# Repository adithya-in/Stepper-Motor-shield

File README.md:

# Stepper Motor Shield — PID Position Control + S-Curve

PIC32MK0512MCJ064 firmware driving a NEMA17 stepper via TB6600 driver with AS5047U
magnetic encoder feedback. Controlled over USB serial (115200 baud) or web dashboard.

**Achieved accuracy: ±1–3 encoder counts = 0.022°–0.066°** (limited by encoder noise floor).

**Clock speed note:** All testing done at **48 MHz** SYSCLK (SPLL from 8 MHz FRC). Target production clock is **10 MHz** (external crystal or lower PLL) — testing pending.

## Project Status

| Area | Status |
|------|--------|
| **Firmware** | **Complete** — v6.2.0 tested and verified at 48 MHz (SPLL, 115200 baud, auto-tune capped) |
| **Hardware testing** | **Complete** — NEMA17 + TB6600 characterized at 24V and 31V (see test data below) |
| **Schematic** | **Complete** — KiCad schematic for PIC32MK + TMC2660 + AS5047D + CAN + USB-C (`hardware/Motorshield v6.kicad_sch`) |
| **PCB layout** | **In progress** — routing and layout yet to be finished |
| **10 MHz migration** | **Pending** — clock-dependent formulas need recalculation and retesting |

## Quick Start

```bash
# Flash firmware (via MDB)
rm -rf ~/.mplabcomm
/Applications/microchip/mplabx/v6.30/mplab_platform/bin/mdb.sh flash.mdb

# Connect serial
screen /dev/cu.usbmodemBUR2143200772 115200

# Start dashboard
cd dashboard && npm install && node server.js
# → http://localhost:3000
```

**Power cycle the PKoB4** (unplug/replug USB) after flashing — VCOM gets stuck otherwise.

## Serial Commands

All commands support both **legacy** and **Phase 1** formats. Legacy commands are preserved
so the dashboard and existing scripts continue working.

### Legacy Commands

| Command | Action | Range |
|---------|--------|-------|
| **Position Control** | | |
| `T=<pos>` | Move to absolute position (encoder counts, negative OK) | ±2M |
| `STOP` | Emergency stop — hold position, reset integrator | — |
| `HOME` | Set current position = 0 AND target = 0 | — |
| `ZERO` | Set current position = 0 (leave target unchanged) | — |
| `CLEAR` | Clear fault, re-init motor driver | — |
| **Open-Loop Motor Test** | | |
| `ON` | Enable motor + start spinning at last speed (default 100) | — |
| `OFF` | Disable motor, exit open-loop mode | — |
| `CW` | Set direction clockwise | — |
| `CCW` | Set direction counter-clockwise | — |
| `SPEED=<n>` | Set step rate for open-loop mode | 10–100000 |
| **Motion Profile** | | |
| `MAXV=<n>` | Max velocity | ≥1 steps/s |
| `ACCEL=<n>` | Max acceleration | ≥100 steps/s² |
| `JERK=<n>` | Max jerk (S-curve smoothness) | ≥1000 steps/s³ |
| `PROFILE=S` | S-curve — jerk-limited smooth transitions | — |
| `PROFILE=T` | Trapezoidal — instant acceleration changes | — |
| **PID Tuning** | | |
| `KP=<n>` | Proportional gain | 0–99999 |
| `KI=<n>` | Integral gain | 0–99999 |
| `KD=<n>` | Derivative gain | 0–99999 |
| `TOL=<n>` | At-target tolerance | 0–1000 counts |
| `FT=<n>` | Fault threshold (checked only at rest) | 1–100000 counts |
| **Diagnostics** | | |
| `GET` | One-shot config dump | — |
| **Multi-Point Queue** | | |
| `Q=<pos>,<pos>,...` | Load queue (2–32 points) and start sequential execution | — |
| `DWELL=<ms>` | Set inter-point dwell delay (0–30000 ms) | — |
| `QSTOP` | Abort queue mid-execution | — |

### Phase 1 Commands (Colon-Separated)

| Command | Action | Example |
|---------|--------|---------|
| **Move** | | |
| `m:<speed>:<pos>` | Move to position at given speed (sets MAXV temporarily) | `m:20000:80000` |
| **Enable** | | |
| `en:1` | Enable closed-loop servo (hold current position) | `en:1` |
| `en:0` | Disable motor (release) | `en:0` |
| **Zero** | | |
| `z` | Set current encoder position as zero | `z` |
| **Coil Current (stored)** | | |
| `i:<mA>` | Set coil current limit (stored value, 100–5000 mA) | `i:800` |
| **Microstep (stored)** | | |
| `us:<n>` | Set microstep setting (1/2/4/8/16/32) | `us:16` |
| **PID Gains** | | |
| `pid:<kp>:<ki>:<kd>` | Set proportional, integral, derivative gains | `pid:50:5:10` |
| **Telemetry** | | |
| `tlm:1:<ms>` | Enable status stream at N ms period | `tlm:1:50` |
| `tlm:0` | Disable status stream | `tlm:0` |
| **Multi-Point Queue** | | |
| `q:<pos1>:<pos2>:...` | Load queue (2–32 points) and start sequential execution | `q:10000:20000:30000` |
| `dwell:<ms>` | Set inter-point dwell delay | `dwell:1000` |
| `qstop` | Abort queue mid-execution | `qstop` |
| **Status Query** | | |
| `st?` | One-shot status: position, velocity, error, flags | `st?` |

### Response Format

All commands acknowledge:
```
OK <command>=<value>\r\n
```
or
```
ERR UNKNOWN\r\n
```

### Automatic Status Stream (10 Hz default)

```
P:<position>,E:<error>,V:<velocity>,T:<target>,F:<fault>,M:<moving>,A:<at_target>,Q:<qidx>,QL:<qlen>\r\n
```

Set period with `tlm:1:<ms>` (10–10000 ms), disable with `tlm:0`.

### st? Response (one-shot)

```
p:<position>,v:<velocity>,e:<error>,f:<flags>\r\n
```

Flags bitmask:
- bit 0: fault
- bit 1: moving
- bit 2: at_target
- bit 3: open_loop

### GET Response

```
T=<target>,P=<position>,E=<error>,V=<velocity>,KP=<kp>,KI=<ki>,KD=<kd>,MAXV=<maxv>,ACCEL=<accel>,JERK=<jerk>,TOL=<tol>,FT=<ft>,PROFILE=<S|T>,I=<mA>,US=<microstep>,QLEN=<n>,QIDX=<n>,DWELL=<ms>\r\n
```

## Usage Examples

### Basic Move

```
> en:1           Enable servo (holds current position)
OK en:1
> m:20000:50000  Move to position 50000 at 20000 steps/s
OK m:20000:50000
> st?            Check status
p:50000,v:0,e:0,f:4
```

### Snappy Move (profile feed-forward)

The motor runs at full commanded speed until the stopping distance
(`v² / (2·accel_limit)`) from target, then decelerates hard. The PID
acts as a trim, active only near the target.

```
> PROFILE=T      Trapezoidal profile (instant accel changes)
> ACCEL=500000   Fastest ramp
> MAXV=50000     Top speed
OK PROFILE=T
OK ACCEL=500000
OK MAXV=50000
> m:50000:100000 Move at 50000 steps/s — reaches full speed in ~100ms
OK m:50000:100000
```

### PID Tuning

```
> pid:30:2:5     Set Kp=30, Ki=2, Kd=5
OK pid:30:2:5
> GET            Verify all params
T=10000,P=10000,E=0,V=0,KP=30,KI=2,KD=5,...
```

### Auto-Tune

Relay-based Ziegler-Nichols PID tuning. The motor oscillates around a target, measures ultimate gain (Ku) and period (Tu), then applies:

```
Kp = 0.6 × Ku × 100    (capped at 10000)
Ki = 1.2 × Ku / Tu      (capped at 1000)
Kd = 0.075 × Ku × Tu    (capped at 10000)
```

Send `TUNE` to start. The motor will:
1. Move to current position + 3000 counts
2. Begin relay oscillation (±3000 steps/s relay velocity)
3. After 4+ full cycles, compute PID gains
4. Report: `OK TUNE:Kp=...,Ki=...,Kd=...,amp=...,Tu=...`
5. Return to original target

Caps on auto-tune output prevent excessive gains that cause oscillation — particularly Kd, which can destabilize the motor at high values.

### Telemetry Stream

```
> tlm:1:200      Stream every 200ms
OK tlm:1:200
P:5000,E:-2,V:150,T:5000,F:0,M:0,A:1
P:5000,E:-1,V:0,T:5000,F:0,M:0,A:1
...
> tlm:0          Stop streaming
OK tlm:0
```

### Multi-Point Queue

```
> DWELL=2000     Set 2 second pause between points
OK DWELL=2000
> Q=10000,30000,50000,20000  Load 4-waypoint queue
OK Q=4 points
> ...automatically moves: 10000 → 30000 → 50000 → 20000...
                Each arrival: 2s dwell → next move
> QSTOP          Abort mid-sequence
OK QSTOP
```

Queue is automatically aborted on any manual move (`T=`, `m:`), `STOP`, `OFF`, or `en:0`.

## Accuracy

The system achieves **±1–3 encoder counts** following error at rest.

| Domain | Value |
|--------|-------|
| 1 encoder count | 360° / 16384 = **0.022°** |
| Typical error | 1–3 counts = **0.022°–0.066°** |
| AS5047U non-linearity | ±0.05° = ~±2 counts |
| With 10mm leadscrew | 1 count ≈ **0.6 µm** |

The error is at the encoder's own noise floor. No further improvement possible
without a higher-resolution encoder.

## Non-Volatile Config

All tuning parameters (Kp, Ki, Kd, max_vel, accel_limit, jerk_limit, tolerance,
fault_thr, profile, coil_current, microstep) are automatically saved to the last
flash page when changed. Persist across power cycles.

- **Flash address**: last page of 512KB (0x1D07F000)
- **Save strategy**: 100ms debounce after last parameter change
- **Integrity**: magic word (0xBEADC0DE) + XOR checksum validated on load
- **Defaults**: used if flash is blank or corrupted

## Motion Profiles

### S-Curve (`PROFILE=S`)
Jerk-limited acceleration:

```
acceleration:  ──/‾‾‾‾‾‾\──  (ramps up/down at JERK rate)
velocity:      ──/‾‾‾‾‾‾\──  (rounded S-shaped transitions)
```

- Jerk limits how fast acceleration changes
- Lower JERK = smoother but slower moves
- Three phases: smooth accel → coast → smooth decel

### Trapezoidal (`PROFILE=T`)
Instant acceleration changes:

```
acceleration:  ──╯‾‾‾‾‾‾╰──  (square wave)
velocity:      ──/‾‾‾‾‾‾\──  (sharp V-shaped ramps)
```

- ACCEL limits the slope of velocity ramps
- Reaches target speed faster than S-curve at same ACCEL
- Higher mechanical stress at transitions

### Profile Feed-Forward (v5.1.2+)

The velocity target is computed from a motion profile, not from PID error.
The motor maintains full commanded speed until the stopping distance from target,
then decelerates at the ACCEL rate. PID adds only a small trim for fine positioning.

```
raw_vel = profile_velocity(error) + pid_trim
profile_vel = max_vel (if far) or linear decel ramp (near target)
pid_trim    = (Kp·error + Ki·integral + Kd·derivative) / 100
```

Anti-windup: integral resets during moves, only active near target.
Auto-tune output capped at Kp≤10000, Ki≤1000, Kd≤10000 to prevent excessive gains.

## Wiring

See [PINOUT.md](docs/PINOUT.md) for complete pin mapping.

### TB6600 Common-Anode Summary

| TB6600 | PIC32MK | Note |
|--------|---------|------|
| PUL+ | RPB15 (OC1 PWM) | Step pulses, 50% duty |
| DIR+ | RPB14 (GPIO) | LOW=CW, HIGH=CCW |
| ENA+ | RPB13 (GPIO) | **LOW=enable**, HIGH=disable |
| PUL-/DIR-/ENA- | GND | All three tied together |

### TB6600 DIP Switches
- S1/S2/S3: per motor current rating
- S4/S5/S6: S4 ON, S5 ON, S6 ON = 1/32 microstep (6400 steps/rev)

## Dashboard

Web-based UI on port 3000:

```
dashboard/
├── server.js          # Express + WebSocket + serial bridge
├── package.json
└── public/
    ├── index.html     # UI layout
    ├── app.js         # Client logic
    └── styles.css     # Dark theme
```

### Features
- Position display: target / actual with bar indicator
- Status: error, velocity, fault, moving, at-target
- Motor Test card: ON/OFF, CW/CCW, speed slider (up to 50000 steps/s)
- PID sliders: Kp (0–50000), Ki (0–10000), Kd (0–50000)
- Auto-tune button: relay-based Ziegler-Nichols tuning, results shown with slider label sync
- TLM toggle: enable/disable telemetry stream
- Motion Profile: S-curve / Trapezoidal toggle
- ACCEL and JERK number inputs with Set buttons
- MAXV, Tolerance, Fault Threshold inputs
- GET response parsing: position, error, velocity, TOL, FT fields

### Architecture

```
Firmware (PIC32MK) ←→ Serial (115200) ←→ server.js ←→ WebSocket ←→ browser
```

## Firmware Architecture

**Clock:** Currently runs at **48 MHz** (SPLL from 8 MHz FRC). Target for production: **10 MHz** — all clock-dependent formulas (core timer, UART baud, step pulse generation, auto-tune timing) will need recalculation. Testing at 10 MHz is pending.

| Component | Peripheral | Rate | Purpose |
|-----------|-----------|------|---------|
| Position loop | Timer3 ISR | 1 kHz | Profile → PID trim → smoother → velocity |
| Step generation | OC1 + Timer2 PWM | Variable | Hardware step pulses, 50% duty |
| Encoder | QEI1 | Continuous | AS5047U ABI, 16384 counts/rev |
| UART | UART1 | 115200 baud | Command + telemetry |
| NVM flash | Self-write | On change | Config storage (last flash page) |
| Status stream | Main loop | Configurable | P:E:V:T:F:M:A:Q:QL telemetry |

### Algorithm

```
error = target_pos - encoder_read()

// Profile feed-forward velocity
stop_dist = max_vel² / (2 × accel_limit)     // stopping distance
if abs(error) > stop_dist:
    profile_vel = max_vel × sign(error)       // cruise
else:
    profile_vel = max_vel × error / stop_dist // decel ramp

// PID trim
pid_trim = (Kp×error + Ki×integral + Kd×derivative) / 100

// Combined, fed into accel/jerk smoother
raw_vel = profile_vel + pid_trim

// Accel/jerk smoother → sm_vel → motor steps
```

### Resolution

| Aspect | Value |
|--------|-------|
| Motor steps/rev | 200 (NEMA17, 1.8°/step) |
| Microstep setting | **1/32** (S4 ON, S5 ON, S6 ON) |
| Steps per revolution | **6400** |
| Encoder PPR | 4096 (AS5047U) |
| Encoder counts/rev (4× QEI) | 16384 |
| Position resolution | 360° / 16384 = **0.022°** per count |

## Voltage-Dependent Limits

At **1/32 microstep** (6400 steps/rev). Firmware accepts any positive value; the
practical limit is set by the motor driver and supply voltage. Empirically determined
guidelines (no load, idle condition):

| Supply Voltage | MAXV (steps/s) | MAXV (RPM) | ACCEL (steps/s²) | Notes |
|----------------|----------------|------------|------------------|-------|
| 31V | 280,000 | 2,625 | 2,700,000 | Best reliable: 1725 mm/s, Kp=2121 Ki=46. All tests at 48 MHz — 10 MHz testing pending |
| 24V | 250,000 | 2,344 | 3,200,000 | At ≥2.5A coil current, smooth with heating. All tests at 48 MHz — 10 MHz testing pending |
| 12V | 50,000 | 469 | 5,000,000 | Reduced max velocity. All tests at 48 MHz — 10 MHz testing pending |

**31V characterization** (from `docs/TESTS.md`):
- MAXV 300k with 3.2M ACCEL reaches 1902 mm/s (Kp 50–1000, Ki=5, Kd=0)
- Kp >~2000 with Ki > 0 causes oscillation at 31V; best results use moderate Kp
- Trade-off: higher MAXV requires lower ACCEL and vice versa
- Kd was 0 in all 31V tests — derivative not needed with proper Kp/Ki balance

**RPM formula:** `RPM = (steps/s × 60) ÷ steps_per_rev` where `steps_per_rev = 6400` at 1/32.

## Releases

| Tag | Date | Description |
|-----|------|-------------|
| **v6.2.0** | 2026-06-20 | **Auto-tune caps restored, 31V test data.** Kp≤10000/Ki≤1000/Kd≤10000 caps restored on auto-tune output (prevents oscillation from excessive gains). 31V characterization: 280k MAXV / 2.7M ACCEL / 1725 mm/s reliable belt speed. |
| **v6.1.0** | 2026-06-17 | **SPLL clock (48 MHz), 115200 baud, no command limits.** FRC→SPLL migration. All clock timing fixed. MAXV/ACCEL/JERK upper limits removed. Dashboard TLM toggle. |
| **v6.0.0** | 2026-06-15 | **Phase 1 complete.** `docs/BUGS_AND_LESSONS.md` — full 24+ bug knowledge base. Dashboard activeElement input protection. |
| **v5.2.0** | 2026-06-12 | Multi-point queue (Q=/q:), DWELL, QSTOP, dashboard queue card |
| **v5.1.4** | 2026-06-12 | Dashboard UI ranges match firmware; ACCEL/JERK number inputs; accuracy ±1–3 counts |
| **v5.1.3** | 2026-06-12 | Snappier defaults: MAXV=5000, ACCEL=50000, JERK=500000; ranges increased 5–10× |
| **v5.1.2** | 2026-06-12 | Profile feed-forward velocity; full speed until stopping distance; PID trim only near target |
| **v5.1.1** | 2026-06-12 | NVM flash config: all settings persist across power cycles |
| **v5.1.0** | 2026-06-12 | Phase 1 commands (colon-separated), Kd, configurable telemetry |
| **v5.0.1** | 2026-06-11 | Trapezoidal profile, dashboard toggle, ACCEL/JERK commands |
| **v5.0.0** | 2026-06-11 | PID + S-curve + open-loop test + 6 bug fixes |
| **v4.0.0** | 2026-06-10 | UART serial fixes |
| **v3.1.0** | 2026-06-09 | Open-loop speed control |
| **v3.0.0** | 2026-06-09 | Closed-loop position control |
| **v2.0.0** | 2026-06-09 | Stepper control + encoder |
| **v1.0.0** | 2026-06-08 | Encoder-only firmware |

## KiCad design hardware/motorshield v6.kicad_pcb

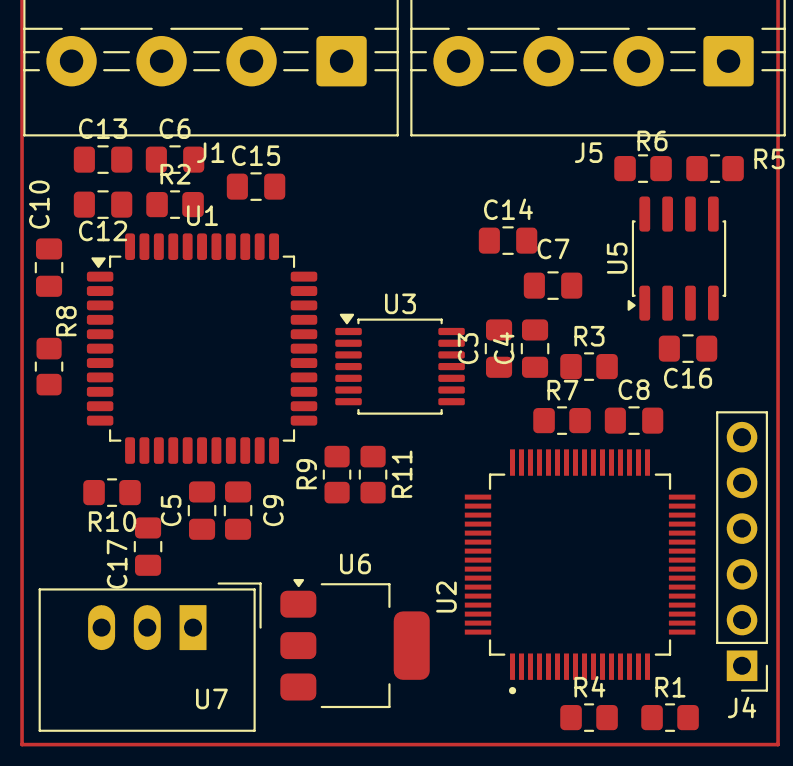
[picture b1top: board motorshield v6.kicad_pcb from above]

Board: 2 copper layers, 34 parts (0 on the bottom side), 42 nets, no tracks yet.

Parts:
C3: 10 µF; C_0805_2012Metric_Pad1.18x1.45mm_HandSolder
C4, C5, C6: 0.1 µF; C_0805_2012Metric_Pad1.18x1.45mm_HandSolder
C7, C8: 21 pF; C_0805_2012Metric_Pad1.18x1.45mm_HandSolder
C9, C12, C13: 1µF; C_0805_2012Metric_Pad1.18x1.45mm_HandSolder
C10: 100nF; C_0805_2012Metric_Pad1.18x1.45mm_HandSolder
C14, C16: 100nF/50V; C_0805_2012Metric_Pad1.18x1.45mm_HandSolder
C15: 220nF; C_0805_2012Metric_Pad1.18x1.45mm_HandSolder
C17: 470nF; C_0805_2012Metric_Pad1.18x1.45mm_HandSolder
J1, J5: Conn_01x04; TerminalBlock_MaiXu_MX126-5.0-04P_1x04_P5.00mm
J4: Conn_01x06; PinHeader_1x06_P2.54mm_Vertical
R1, R4, R7: 1K; R_0805_2012Metric_Pad1.20x1.40mm_HandSolder
R2: 10K; R_0805_2012Metric_Pad1.20x1.40mm_HandSolder
R3: 0 Ω; R_0805_2012Metric_Pad1.20x1.40mm_HandSolder
R5, R6: 120; R_0805_2012Metric_Pad1.20x1.40mm_HandSolder
R8, R11: 0R075; R_0805_2012Metric_Pad1.20x1.40mm_HandSolder
R9, R10: 10R; R_0805_2012Metric_Pad1.20x1.40mm_HandSolder
U1: TMC2660; LQFP-44_10x10mm_P0.8mm
U2: PIC32MK0512MCJ064T-I_PT; PIC32MK0512MCJ064-I_PT
U3: AS5047D; TSSOP-14_4.4x5mm_P0.65mm
U5: MCP2562-E-SN; SOIC-8_3.9x4.9mm_P1.27mm
U6: AMS1117-3.3; SOT-223-3_TabPin2
U7: TSR_1-2450; Converter_DCDC_TRACO_TSR-1_THT

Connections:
+3.3V: C3.1, C4.1, C5.1, C9.1, C16.1, J4.2, R2.2, U1.40 (VCC_IO), U2.10 (VDD), U2.19 (AVDD), U2.26 (VDD), U2.38 (VDD), U2.57 (VDD), U3.12 (VDD3V3), U5.5 (Vio), U6.2 (VO)
+5V: U6.3 (VI), U7.3 (Vout)
+40V: C10.2, C12.1, C13.1, C14.1, C15.1, J5.4, U1.4 (VSA), U1.30 (VSB), U1.36 (VS), U3.11 (VDD), U7.1 (Vin)
/CAN1_RX: U2.36 (AN46/CVD46/RPA14/RA14), U5.4 (RXD)
/CAN1_TX: U2.37 (AN47/CVD47/RPA15/RA15), U5.1 (TXD)
/CANH: J5.2, R6.2
/CANL: J5.1, R5.2
/CSN: U1.18 (~CS), U2.32 (FLT15/RPB4/SCL2/RB4)
/Clock: U2.15 (PGD3/VREF-/OA2IN-/AN2/C2IN1-/RPB0/CTED2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), U3.2 (CLK)
/DIR: U1.41 (DIR), U2.2 (RPB14/PWM1H/RB14)
/ENABLE: U1.19 (~EN), U2.63 (RPB13/PWM2L/CTPLS/RB13)
/Encoder A: U2.4 (AN19/CVD19/RPG6/PWM7L/RG6), U3.7 (A)
/Encoder B: U2.5 (AN18/CVD18/RPG7/PWM7H/RG7), U3.6 (B)
/MCLR: J4.1, R1.2, U2.7 (~MCLR)
/Miso: U2.17 (PGC1/OA1IN+/AN4/C1IN1+/C1IN3-/C2IN3-/RP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), U3.3 (MISO)
/Mosi: U2.16 (PGC3/OA1OUT/VREF+/AN3/C1IN4-/C4IN2-/RPB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), U3.4 (MOSI)
/Motor A+: J1.4, U1.2 (OA1), U1.3 (OA1), U1.7 (OA1), U1.8 (OA1)
/Motor A-: J1.3, U1.5 (OA2), U1.6 (OA2), U1.10 (OA2), U1.11 (OA2)
/Motor B+: J1.2, U1.26 (OB1), U1.27 (OB1), U1.31 (OB1), U1.32 (OB1)
/Motor B-: J1.1, U1.23 (OB2), U1.24 (OB2), U1.28 (OB2), U1.29 (OB2)
/NC: J4.6, U1.1 (n.c.), U1.33 (n.c.), U3.8 (W/PWM), U3.9 (V), U3.10 (U), U3.14 (I/PWM)
/OSCI: C8.1, U2.39 (OSCI/CLKI/AN49/CVD49/RPC12/RC12)
/OSCO: R3.2, U2.40 (OSCO/CLKO/RPC15/RC15)
/SCK: U1.16 (SCK), U2.43 (PGD2/RPB5/SDA1/RB5)
/SDI: U1.15 (SDI), U2.46 (OA5OUT/AN25/CVD25/C5IN4-/RPB7/SCK1/INT0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)
/SDO: U1.14 (SDO), U2.44 (PGC2/RPB6/SCL1/RB6)
/STEP: U1.42 (STEP), U2.3 (RPB15/PWM1L/RB15)
/cs: U2.18 (PGD1/OA1IN-/AN5/CTCMP/C1IN1-/RTCC/RPB3/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), U3.1 (~CS)
GND: C3.2, C4.2, C5.2, C6.2, C7.2, C8.2, C9.2, C10.1, C12.2, C13.2, C14.2, C16.2, C17.1, J4.3, J5.3, R4.1, R7.2, R8.2, R11.2, U1.17 (GND), U1.39 (GND), U1.43 (TST_MODE), U1.44 (GND), U2.9 (VSS), U2.20 (AVSS), U2.25 (VSS), U2.41 (VSS), U2.56 (VSS), U3.5 (TST), U3.13 (GND), U5.2 (VSS), U5.8 (STBY), U6.1 (GND), U7.2 (GND)
unnamed: C7.1, R3.1
unnamed: C6.1, R1.1, R2.1
unnamed: C17.2, U1.13 (5VOUT)
unnamed: R8.1, R10.2, U1.9 (BRA)
unnamed: R9.2, R11.1, U1.25 (BRB)
unnamed: R10.1, U1.12 (SRA)
unnamed: R9.1, U1.22 (SRB)
unnamed: C15.2, U1.35 (VHS)
unnamed: R4.2, U2.1 (TCK/RPA7/PWM4L/RA7), U2.11 (AN10/CVD10/RPA12/FLT13/RA12), U2.12 (AN9/CVD9/RPA11/FLT14/RA11), U2.13 (OA2OUT/AN0/C2IN4-/C4IN3-/RPA0/RA0), U2.14 (OA2IN+/AN1/C2IN1+/RPA1/RA1), U2.31 (TDI/DAC2/AN26/CVD26/RPA8/SDA2/RA8), U2.33 (OA5IN+/AN24/CVD24/C5IN1+/C5IN3-/RPA4/RA4), U2.64 (TDO/PWM4H/RA10)
unnamed: R7.1, U2.21 (OA3OUT/AN6/CVD6/C3IN4-/C4IN1+/C4IN4-/RP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), U2.22 (OA3IN-/AN7/CVD7/C3IN1-/C4IN1-/RPC1/RC1), U2.23 (OA3IN+/AN8/CVD8/C3IN1+/C3IN3-/RPC2/FLT3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), U2.24 (AN11/CVD11/C1IN2-/FLT4/RC11), U2.27 (AN12/CVD12/C2IN2-/C5IN2-/FLT5/RE12), U2.28 (AN13/CVD13/C3IN2-/FLT6/RE13), U2.29 (AN14/CVD14/RPE14/FLT7/RE14), U2.30 (AN15/CVD15/RPE15/FLT8/RE15), U2.34 (AN40/CVD40/RPE0/RE0), U2.35 (AN41/CVD41/RPE1/RE1), U2.42 (RD8), U2.45 (DAC1/AN48/CVD48/RPC10/RC10), U2.47 (SOSCI/RPC13/RC13), U2.50 (TRCLK/RPC6/PWM6H/RC6), U2.51 (TRD0/RPC7/PWM6L/RC7), U2.52 (TRD1/RPC8/PWM5H/RC8), U2.53 (TRD2/RPD5/PWM9H/RD5), U2.54 (TRD3/RPD6/PWM9L/RD6), U2.55 (RPC9/PWM5L/RC9), U2.58 (RPF0/PWM8H/RF0), U2.59 (RPF1/PWM8L/RF1)
unnamed: U2.6 (AN17/CVD17/RPG8/RG8), U2.8 (AN16/CVD16/RPG9/FLT12/RG9)
unnamed: R6.1, U5.7 (CANH)
unnamed: R5.1, U5.6 (CANL)

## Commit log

2026-06-06 Initial commit: AS5047U encoder QEI + UART firmware for PIC32MK MCJ Curiosity Pro
2026-06-06 Add web dashboard, change UART baud to 115200
2026-06-08 Fix UART serial output: PB1DIV clock divider, PPS lock bits, and baud rate
    Bugs fixed (in order of discovery):
    1. CFGCON address was 0xBF80F610 (nonexistent) → changed to 0xBF800000
    - This caused PPS unlock to crash the MCU, no code ever ran
    2. PB1CLK defaults to SYSCLK/2 (4 MHz), not 8 MHz
    - Hardcoded PB_CLOCK=8000000 gave wrong baud (8.5% error at 38400)
    - Changed to PB_CLOCK=4000000 with UART_BAUD=19200 (0.16% error)
2026-06-08 Add CHANGELOG.md for v1.0.0
2026-06-09 v2.0.0: TB6600 stepper control + encoder feedback + full test documentation
    - Add OC1-based step generation (Timer2 PWM, RPB15, 10 kHz)
    - Add direction control (RPB14) and enable (RPB13, LOW=enable)
    - CW 5s → CCW 5s test loop with UART RPM reporting
    - Fix ENA polarity for common-anode wiring (ENA_ON=0)
    - docs/TESTS.md: full journey from Arduino prototyping through PIC32MK
    - docs/PINOUT.md: complete wiring reference with physical pin numbers
2026-06-09 v3.0.0: Closed-loop position control + PI controller + web dashboard
    - Timer3 position control loop at 1 kHz with PI controller
    - OC1/Timer2 variable-rate step generation (10-5000 steps/s)
    - Following error computation with configurable fault threshold
    - Software zero reference (HOME command)
    - Point-to-point moves with configurable position tolerance
    - Coil current limit enforced via MAXV cap
2026-06-09 v3.1.0: Speed control mode — motor spins from browser slider
    - Replace closed-loop position control with open-loop speed control
    - Commands: ON OFF CW CCW SPEED <steps/s>
    - Dashboard: RPM gauge, speed slider (0-10000), direction toggle, start/stop
    - Encoder RPM feedback displayed live in browser
    - Clean build, no errors
2026-06-09 Auto-start motor at 2000 steps/s CW on boot
2026-06-09 Add encoder position display to dashboard
2026-06-09 Single-char commands for instant motor control (0=off 1=on 2=cw 3=ccw)
2026-06-09 Fix: configure RPG8 as digital input for UART RX
2026-06-10 v4.0.0: UART serial fixes — U1RXR=10, URXEN=1, OERR handler, SPEED parsing fix
    UART fixes required for reliable serial communication on PIC32MK Curiosity Pro:
    - U1RXR = 10 (was 1) — correct PPS input mapping for RPG8 as U1RX
    - U1STAbits.URXEN = 1 — explicitly enable receiver (not set by UARTEN)
    - uart_clear_oerr() — clear overrun errors and flush RX FIFO
    - Single-char commands only at rx_idx == 0 — prevents digit '0'
    in SPEED 5000 from matching STOP handler
2026-06-10 Fix PID position control: interrupt, fault, acceleration, and hold fixes
    ## Bugs fixed
    1. **Timer3 ISR never fired** — IFS0/IEC0 used bit 12 (INT4) instead
    of bit 14 (Timer3) on PIC32MK0512MCJ064. PID control loop was
    completely dead since firmware inception.
    2. **Missing global interrupt enable** — no __builtin_enable_interrupts()
    call. Added in main() after fixing bit 14.
2026-06-11 S-curve trajectory: jerk-limited acceleration for smooth motion
2026-06-11 Trapezoidal + S-curve profile selection via PROFILE=S/T command
2026-06-11 Dashboard: profile toggle (S-curve/Trapezoidal) + ACCEL/JERK sliders
2026-06-11 Full documentation: README + CHANGELOG with all commands, profiles, wiring
2026-06-12 v5.1.0 — Phase 1 commands: colon-separated opcode format, Kd, configurable telemetry
2026-06-12 v5.1.1 — NVM flash config: parameters persist across power cycles
2026-06-12 v5.1.1 docs: CHANGELOG + README
2026-06-12 v5.1.2 — profile feed-forward: full speed until stopping distance, PID trim only near target
2026-06-12 v5.1.2 docs: CHANGELOG
2026-06-12 v5.1.3 — snappier defaults: MAXV=5000, ACCEL=50000, JERK=500000; range bumps: MAXV→50000, ACCEL→500000, JERK→10M
2026-06-12 v5.1.3 docs: CHANGELOG
2026-06-12 v5.1.4 — dashboard: UI ranges match new firmware (MAXV=50000, ACCEL=500000, JERK=10M); ACCEL/JERK changed to number inputs with Set button; server.js parses ACCEL/JERK/MAXV/KD/I/US from GET
2026-06-12 v5.1.4 docs: CHANGELOG
2026-06-12 v5.1.4 docs: full README rewrite with accuracy specs, range tables, profile feed-forward explanation; CHANGELOG updated
2026-06-12 v5.2.0 multi-point queue: Q=, DWELL, QSTOP, dashboard queue card, docs
2026-06-12 fix: make status regex backward-compatible, Q= parsing handles spaces
2026-06-15 v5.3.0 — auto-tune: relay-based Ziegler-Nichols PID tuning, Kd, dashboard UI
2026-06-15 v6.0.0 — Phase 1 complete: BUGS_AND_LESSONS.md knowledge base, dashboard activeElement fix
2026-06-15 fix: add Cache-Control no-store and cache-busting meta tags to prevent stale dashboard
2026-06-15 raise MAXV limit 50000 -> 100000 in firmware and dashboard
2026-06-15 Revert "raise MAXV limit 50000 -> 100000 in firmware and dashboard"
    This reverts commit d088e7e43fe713ce4c691078f8c89634434a5e24.
2026-06-15 raise MAXV limit 50000 -> 100000
2026-06-15 raise ACCEL limit 500k -> 5M
2026-06-15 fix: pending-field guard prevents telemetry overwrite after Set; add units to dashboard labels
2026-06-15 fix: CONFIG_DATA_WORDS 12->11 (struct has 11 fields, 12th was garbage breaking checksum)
2026-06-15 fix: immediate field update on Set, 250ms telemetry guard, element-based pending tracking
2026-06-15 fix: auto-send GET 200ms after Set to force parameter refresh
2026-06-15 Fix dashboard value-update bugs
    - Server broadcast leaked stale config fields (maxv/accel/jerk) into every
    telemetry broadcast, overwriting edited input fields. Now broadcasts only
    the fields that actually changed per line.
    - Initial GET fired from ws.onopen before serial connected, so it was
    silently dropped. GET now triggers from updateConnection() when
    connected becomes true.
2026-06-17 v6.1.0: SPLL clock (48 MHz), 115200 baud, no command limits
    Clock architecture migrated from FRC to SPLL for reliable 115200 baud.
    All clock-dependent timing formulas fixed (msleep, motor_set_speed,
    auto-tune Tu, config save). Removed hard upper limits on MAXV, ACCEL,
    JERK. Added flash.mdb MDB script. Dashboard: TLM toggle, 115200 baud
    default, GET field parsing. Docs: microstep 1/32 corrections.
2026-06-17 docs: update TESTS.md with v6.1.0, add consolidated DOCUMENTATION.pdf
2026-06-17 docs: add motor test results (coil current characterization at 24V, 190k steps/s)
2026-06-18 docs: update motor test data with test bench data1 (250k steps/s, 3.2M accel)
2026-06-18 docs: add belt speed and RPM columns to motor test table
2026-06-18 ui: show auto-tune results (Kp/Ki/Kd/amp/Tu) on dashboard next to Tune button
2026-06-19 fix: auto-tune values now update PID slider labels for fine-tuning
2026-06-19 fix: PID slider ranges match firmware (Kp 0-10000, Ki 0-1000, Kd 0-10000)
2026-06-19 remove PID auto-tune caps, raise dashboard PID slider ranges to 50000
2026-06-20 v6.2.0: restore auto-tune caps (Kp≤10000/Ki≤1000/Kd≤10000), add 31V test data
    - Restore original v5.3.0 auto-tune output caps on Kp (≤10000),
    Ki (≤1000), Kd (≤10000) to prevent excessive gains
    - Add 31V motor test results from motorshieldtest.pdf:
    - 11 test rows sweeping ACCEL/MAXV/Kp/Ki
    - Best result: 280k MAXV / 2.7M ACCEL / 1725 mm/s
    - Kp >~2000 with Ki > 0 causes oscillation at 31V
2026-06-29 add KiCad PCB and schematic files (motorshield v6)
2026-06-29 remove .history embedded git repo from hardware
2026-06-29 add project status report, update 31V test data table, regenerate PDF
2026-06-29 add project report with TOC, status table, 31V test data, pin connections
2026-06-29 update DOCUMENTATION.pdf with report layout, TOC, and status
2026-06-29 DOCUMENTATION.pdf: 12pt readable font, report layout
2026-06-29 add DOCUMENTATION.docx Word version
